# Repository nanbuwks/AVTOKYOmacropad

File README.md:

see https://qiita.com/nanbuwks/items/ea830dcd81b857cce2c1

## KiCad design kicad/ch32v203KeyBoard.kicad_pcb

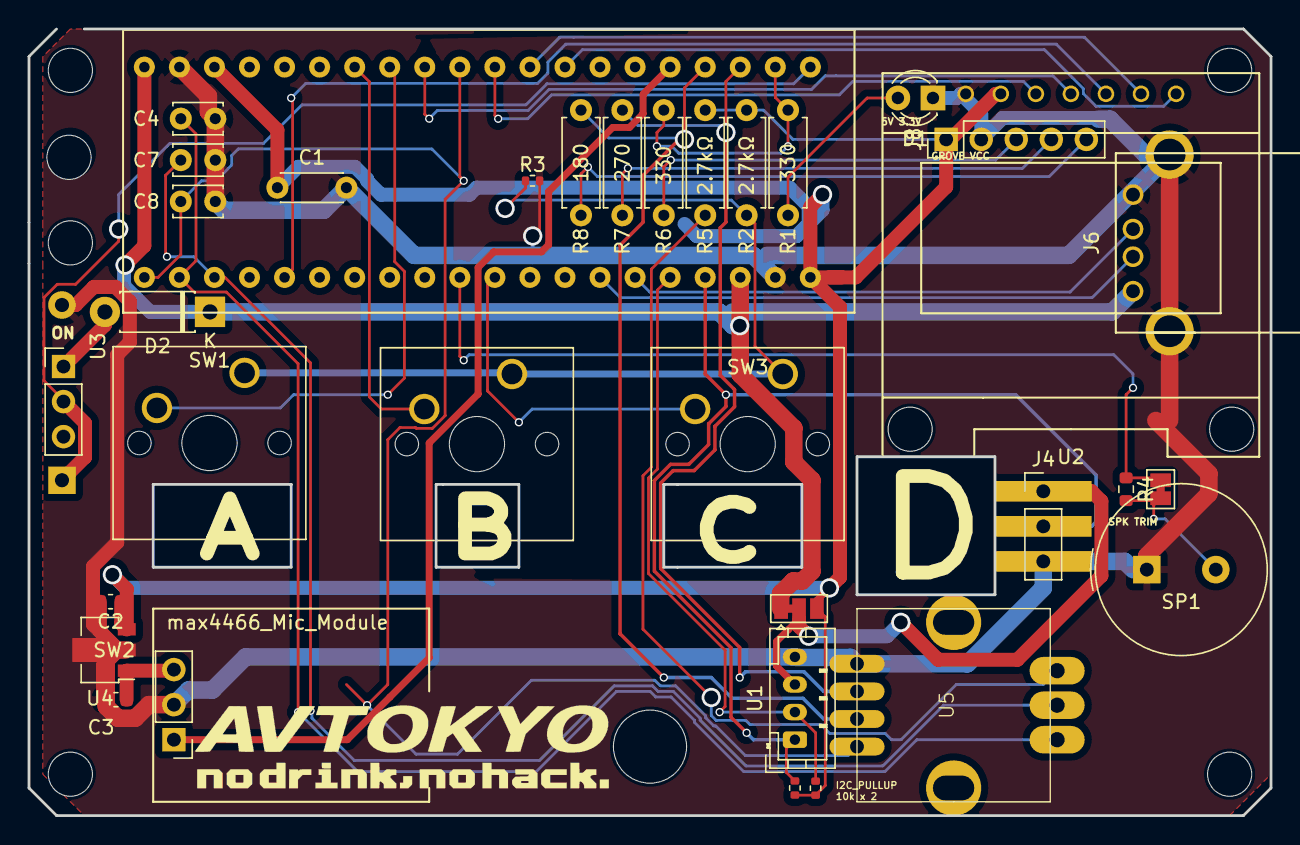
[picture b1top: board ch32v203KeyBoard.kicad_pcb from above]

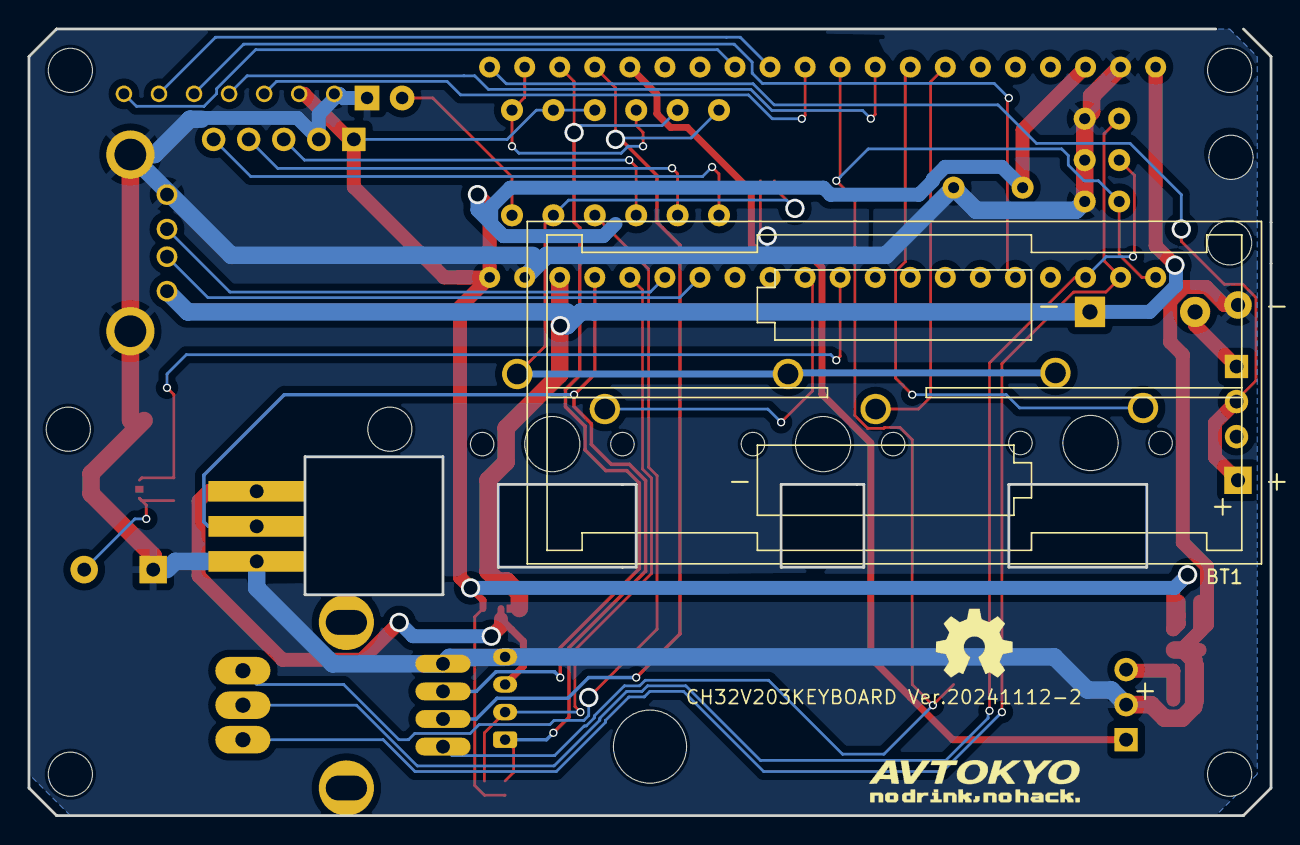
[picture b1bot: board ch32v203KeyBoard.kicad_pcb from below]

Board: 2 copper layers, 90.0 x 57.0 mm, 36 parts (2 on the bottom side), 34 nets.

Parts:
BT1: Battery; BatteryHolder_Keystone_2468_2xAAA
C1: C; C_Disc_D4.3mm_W1.9mm_P5.00mm
C2, C3: 10u; C_0603_1608Metric
C4, C7, C8: C; C_Disc_D3.4mm_W2.1mm_P2.50mm
D1: LED; LED_D3.0mm
D2: 1N6857UR; D_DO-41_SOD81_P7.62mm_Horizontal
J4: NeoPixel; PinHeader_1x03_P2.54mm_Vertical
J6: USB_A; USB_A_Horisontal_Socket_THT
J7: max4466_Mic_Module; PinHeader_1x03_P2.54mm_Vertical
J8: LEDOUT; PinHeader_1x05_P2.54mm_Vertical
JP1: Jumper_2_Bridged; SolderJumper-2_P1.3mm_Bridged_Pad1.0x1.5mm
JP2: GROVE VCC; SolderJumper-3_P1.3mm_Bridged12_Pad1.0x1.5mm
OSHW: 1.1; OSHW_LOGL_SYLK_5mm
R1, R6: 330; R_Axial_DIN0207_L6.3mm_D2.5mm_P7.62mm_Horizontal
R2, R5: 2.7kΩ; R_Axial_DIN0207_L6.3mm_D2.5mm_P7.62mm_Horizontal
R3: OPEN; R_0402_1005Metric
R4: OPEN; R_0603_1608Metric
R7: 270; R_Axial_DIN0207_L6.3mm_D2.5mm_P7.62mm_Horizontal
R8: 180; R_Axial_DIN0207_L6.3mm_D2.5mm_P7.62mm_Horizontal
R9, R10: 10k; R_0402_1005Metric
SP1: SPEAKER; Buzzer_TDK_PS1240P02BT_D12.2mm_H6.5mm
SW1: OK; SW_Cherry_MX_1.00u_PCB
SW2: ↓; SW_Cherry_MX_1.00u_PCB
SW3: ↑; SW_Cherry_MX_1.00u_PCB
SW4: SW_SPDT; PinHeader_1x03_P2.54mm_Vertical
U1: SEEED_GROVE; JST_PH_B4B-PH-K_1x04_P2.00mm_Vertical
U2: OLED_0.96in_SPI
U3: BluePill+; STM32F103C8T6MinimumDevelopBoard
U4: AP130-25Y; SOT-89-3
U5: ROTARYENCODER; EC12PLxxSDVF

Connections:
+5V: D2.1 (K), J6.1 (VBUS), JP2.1 (A), U3.18 (5V), U3.40 (5V)
AVCC: C3.1, J7.3, U4.1 (VO)
BATTERY: BT1.1 (+), SW4.2 (B), U3.21 (VBAT)
CS: U2.7 (CS), U3.28 (PA3)
DC: U2.6 (DC), U3.29 (PA4)
ENCODER1: C4.1, U3.2 (PB13), U5.A
ENCODER2: C7.1, U3.3 (PB14), U5.B
GND: BT1.2 (-), C1.2, C2.2, C3.2, C4.2, C7.2, C8.2, D1.1 (K), J4.3, J6.4 (GND), J6.5 (Shield), J7.2, J8.2, R3.2, SP1.1, U1.4 (Black/GND), U2.1 (GND), U3.19 (GND), U3.39 (GND), U4.2 (GND), U5.1 (GND)
GROVE_SCL: J4.2, R10.2, U1.1 (Yellow/Dn/An/RX/SCL), U3.17 (PB9)
GROVE_SDA: R9.2, U1.2 (White/Dn1/An1/TX/SDA), U3.16 (PB8)
LED1: R1.1, R6.1, U3.22 (PC13)
LED2: R7.1, U3.23 (PC14), U5.2 (LED1)
LED3: R8.1, U3.24 (PC15), U5.3 (LED2)
MIC1: J7.1, U3.25 (PA0)
MOSI: U2.4 (D1), U3.32 (PA7)
unnamed: D1.2 (A), R1.2
unnamed: D2.2 (A), SW4.1 (A)
unnamed: J4.1, JP2.2 (C), U1.3 (Red/VCC)
unnamed: J8.3, R6.2
unnamed: J8.4, R7.2
unnamed: J8.5, R8.2
unnamed: JP1.2 (B), R4.2, SP1.2
unnamed: R2.2, R3.1, SW1.1, SW2.1, SW3.1
unnamed: R5.2, U5.C
OLED_RESET: U2.5 (RST), U3.5 (PA8)
SCK: U2.3 (D0), U3.30 (PA5)
SPEAKER: JP1.1 (A), R4.1, U3.10 (PA15)
SW1: SW1.2, U3.33 (PB0)
SW2: SW2.2, U3.34 (PB1)
SW3: SW3.2, U3.11 (PB3)
SW_ENCODER: C8.1, U3.1 (PB12), U3.31 (PA6), U5.4 (SW)
USB2_DN: J6.2 (D-), U3.14 (PB6)
USB2_DP: J6.3 (D+), U3.15 (PB7)
VCC: C1.1, C2.1, J8.1, JP2.3 (B), R2.1, R5.1, R9.1, R10.1, U2.2 (VCC), U3.20 (3.3V), U3.38 (3.3V), U4.3 (VI)

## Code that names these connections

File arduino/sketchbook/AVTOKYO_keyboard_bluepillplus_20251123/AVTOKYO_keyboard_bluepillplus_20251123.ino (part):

#define ENABLE_ENCODER_LEDS
#ifdef ENABLE_ENCODER_LEDS
constexpr int PIN_LED_ENCODER_1 = PC14;
constexpr int PIN_LED_ENCODER_2 = PC15;
#endif

constexpr int PIN_LED_BUILTIN = PB2;
constexpr int PIN_SWITCH_0 = PB0;
constexpr int PIN_SWITCH_1 = PB1;
constexpr int PIN_SWITCH_2 = PB3;
constexpr int PIN_SWITCH_3 = PA6;
constexpr int PIN_RE1A = PB13;
constexpr int PIN_RE1B = PB14;

#include <RotaryEncoder.h>

RotaryEncoder encoder1(PIN_RE1A, PIN_RE1B, RotaryEncoder::LatchMode::FOUR3);

#include <Adafruit_TinyUSB.h>

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#define SCREEN_HEIGHT 64 // OLED display height, in pixels

// Declaration for SSD1306 display connected using software SPI (default case):
#define OLED_MOSI  PA7
#define OLED_CLK   PA5
#define OLED_DC    PA4
#define OLED_CS    PA3
#define OLED_RESET PA8
Adafruit_SSD1306 display(SCREEN_WIDTH, SCREEN_HEIGHT,
  OLED_MOSI, OLED_CLK, OLED_DC, OLED_RESET, OLED_CS);

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
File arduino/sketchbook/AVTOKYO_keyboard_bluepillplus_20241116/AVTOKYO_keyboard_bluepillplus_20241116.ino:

constexpr int PIN_LED_BUILTIN = PC13;
constexpr int PIN_SWITCH_0 = PB0;
constexpr int PIN_SWITCH_1 = PB1;
constexpr int PIN_SWITCH_2 = PB3;
constexpr int PIN_SWITCH_3 = PB5;
constexpr int PIN_SWITCH_4 = PA4;
constexpr int PIN_SWITCH_5 = PA6;
constexpr int PIN_RE1A = PB13;
constexpr int PIN_RE1B = PB14;
constexpr int PIN_RE2A = PB0;
constexpr int PIN_RE2B = PB1;

// 
#include <RotaryEncoder.h>

RotaryEncoder encoder1(PIN_RE1A, PIN_RE1B, RotaryEncoder::LatchMode::FOUR3);
RotaryEncoder encoder2(PIN_RE2A, PIN_RE2B, RotaryEncoder::LatchMode::FOUR3);


#include <Adafruit_TinyUSB.h>

// HIDレポートIDの定義。機能ごとにIDを割り振り、1つのUSBエンドポイントで複数のHID機能をやりとりする
enum {
  RID_KEYBOARD = 1,
  RID_MOUSE,
  RID_CONSUMER_CONTROL, // メディア操作やボリュームコントロールなど
};

// TinyUSBのテンプレートを利用して、HIDレポートディスクリプタを構築する
uint8_t const desc_hid_report[] = {
    TUD_HID_REPORT_DESC_KEYBOARD(HID_REPORT_ID(RID_KEYBOARD)),
    TUD_HID_REPORT_DESC_MOUSE   (HID_REPORT_ID(RID_MOUSE)),
    TUD_HID_REPORT_DESC_CONSUMER(HID_REPORT_ID(RID_CONSUMER_CONTROL))
};

Adafruit_USBD_HID usb_hid;


// USB HIDの機能をループごとにひとつずつ処理するため、各ステージに番号を割り振る
typedef enum {
    STAGE_KEYBOARD,
    STAGE_MOUSE,
    STAGE_CONSUMER_1,
    STAGE_CONSUMER_2,
    STAGE_COUNT
} STAGE_t;


void setup() {
    // スイッチの入力ピンの初期化。ロータリーエンコーダーのピンはライブラリ側で処理される
    pinMode(PIN_SWITCH_0, INPUT_PULLUP);
    pinMode(PIN_SWITCH_1, INPUT_PULLUP);
    pinMode(PIN_SWITCH_2, INPUT_PULLUP);
    pinMode(PIN_SWITCH_3, INPUT_PULLUP);
    pinMode(PIN_SWITCH_4, INPUT_PULLUP);
    pinMode(PIN_SWITCH_5, INPUT_PULLUP);

    // USB HIDの設定
    usb_hid.setPollInterval(2);
    usb_hid.setReportDescriptor(desc_hid_report, sizeof(desc_hid_report));
    usb_hid.setStringDescriptor("TinyUSB HID Composite");

    usb_hid.begin();
}


void loop() {
  // USB通信の処理
  TinyUSBDevice.task();
  
  if (TinyUSBDevice.mounted()) {
        // USBが接続されているとき

        led_blink(500);

        static STAGE_t stage = 0;

        static long encoder1_position = 0;
        static long encoder2_position = 0;

        // エンコーダーの位置はとりこぼさないように毎回更新する
        encoder1.tick();
        encoder2.tick();

        int dir1 = encoder1.getPosition() - encoder1_position;
        int dir2 = encoder2.getPosition() - encoder2_position;
        bool switch_1 = digitalRead(PIN_SWITCH_0) == LOW;
        bool switch_2 = digitalRead(PIN_SWITCH_1) == LOW;
        bool switch_3 = digitalRead(PIN_SWITCH_2) == LOW;
        bool switch_4 = digitalRead(PIN_SWITCH_3) == LOW;
        bool switch_5 = digitalRead(PIN_SWITCH_4) == LOW;
        bool switch_6 = digitalRead(PIN_SWITCH_5) == LOW;

        if (usb_hid.ready()) {
            // 直前のHIDレポートの送信が完了したら、次のステージを処理する

            switch (stage) {
                // HIDの機能ごとにHIDレポートを組み立てて、送信する

                case STAGE_KEYBOARD:
                    // キーボード
                    {
                        uint8_t modifiers = 0;
                        uint8_t keycode[6] = { 0 };
                        keycode[0] = switch_1 ? 0x04 : 0x00;
                        keycode[1] = switch_2 ? 0x05 : 0x00;
                        keycode[2] = switch_3 ? 0x06 : 0x00;
                        keycode[3] = switch_4 ? 0x07 : 0x00;
                        keycode[4] = switch_5 ? 0x08 : 0x00;

                        usb_hid.keyboardReport(RID_KEYBOARD, modifiers, keycode);
                    }
                    stage = (stage + 1) % STAGE_COUNT;
                    break;

                case STAGE_MOUSE:
                    // マウス
                    {
                        int8_t scroll = 0;
                        uint8_t pan = 0;
                        if (dir1 > 0) {
                            scroll = 4;
                        } else if (dir1 < 0) {
                            scroll = -4;
                        }
                        
                        encoder1_position = encoder1.getPosition();
                        usb_hid.mouseScroll(RID_MOUSE, scroll, pan);
                    }
                    stage = (stage + 1) % STAGE_COUNT;
                    break;

                case STAGE_CONSUMER_1:
                    // コンシューマーコントロール
                    {
                        static unsigned long timer = 0;
                        // static muteswitch_pressed = false;
                        if (millis() - timer > 50) {
                            timer = millis();

                            uint16_t functions = 0;
                            if (switch_6) {
                                functions |= HID_USAGE_CONSUMER_MUTE;
                                // muteswitch_pressed = true;
                            }
                            if (dir2 > 0) {
                                functions |= HID_USAGE_CONSUMER_VOLUME_DECREMENT;
                            } else if (dir2 < 0) {
                                functions |= HID_USAGE_CONSUMER_VOLUME_INCREMENT;
                            }
                            encoder2_position = encoder2.getPosition();

                            usb_hid.sendReport16(RID_CONSUMER_CONTROL, functions);

                            while (digitalRead(PIN_SWITCH_5) == LOW) { delay(1); }
                        }
                        stage = (stage + 1) % STAGE_COUNT;
                        break;
                    }
                
                case STAGE_CONSUMER_2:  // コンシューマーコントロールをすべて解除する
                    usb_hid.sendReport16(RID_CONSUMER_CONTROL, 0x0000);
                    stage = (stage + 1) % STAGE_COUNT;
                    break;

                default:
                    stage = STAGE_KEYBOARD;
            }
        }

    } else {
        // 電源は供給されているがUSBが接続されていないとき（デバッグ用）

        led_blink(1000);
    }
}


void led_blink(unsigned int interval_ms) {
    static unsigned long timer = 0;
    static bool led_on = false;

    if (timer == 0) {
        pinMode(PIN_LED_BUILTIN, OUTPUT);
    }

    if (millis() - timer > interval_ms) {
        timer = millis();
        
        digitalWrite(PIN_LED_BUILTIN, led_on ? LOW : HIGH);
        led_on = !led_on;
    }
}

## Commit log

2025-11-22 add KiCad files
2025-11-22 add arduino board.txt and some sketchbooks
2025-11-22 add a sketchbook
2025-11-23 Add LED activation for the rotary encoder
2025-11-23 add draw bitmap
2025-11-23 Make LED activation for the rotary encoder configurable via #ifdef
